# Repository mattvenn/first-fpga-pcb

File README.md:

# Aim

* Make my first PCB with an FPGA
* Keep it super simple and cheap
* Configured by on-board FLASH or direct with a Raspberry Pi
* 6 PMODs, 2 buttons, 2 LEDs, FLASH for configuration bitstreams.

There is also an ECP5 version of this board: https://github.com/mattvenn/basic-ecp5-pcb

# What a Lattice iCE40 FPGA needs

* A clock input. Has to be provided by an oscillator, it doesn't have a crystal driver.
* 1.2v core supply for the internal logic.
* 2.5v non volatile memory supply. Can be provided via a voltage drop over a diode from 3.3v.
* IO supply for the IO pins, different banks of IO can have different supplies. This design uses 3.3v for all banks.
* Get configured over SPI interface. This can be done directly by a microcontroller or a computer, or the bitstream can be programmed into some FLASH, and the FPGA will read it at boot. If FLASH isn't provided then the bitstream needs to be programmed at every power up or configuration reset. 
* Decoupling capacitors for each IO bank.

# PCB

* [Schematic](hardware/schematic.pdf)
* [OHSPark project](https://oshpark.com/shared_projects/wwMxCKlp) or [Gerbers](hardware/first-fpga-pcb-2020-03-09-fab.zip)
* Cheap, 2 layer board. Probably not so good for fast signals.

# BOM

* FPGA iCE40-HX4K-TQ144 (8k accessible with Icestorm tools)
* 3.3v reg TLV73333PDBVT
* 1.2v reg TLV73312PDBVT
* 12MHz oscillator SIT2001BI-S2-33E-12.000000G
* 16MB FLASH IS25LP016D-JBLE (optional).

# Test

See the [test program](test/top.v). This makes a nice pulsing effect on LED2, and LED1 is the slow PWM clock.
The buttons increase or decrease pulsing speed.

    make prog

Yosys and NextPNR are used to create the bitstream and then it's copied to the Raspberry Pi specified
by PI_ADDR in the [Makefile](test/Makefile). 

[Fomu-Flash](https://github.com/im-tomu/fomu-flash) is used to flash the SPI memory, or program the FPGA directly.

# HW V3: bfcbcf7

* fixed mistakenly removed pullups on io2/3 on SPI flash. This made the system vulnerable to noise while FPGA was reading flash.

# HW V2: 444ba78

* removed a few unnecessary pullups on SPI lines - introduced a fault see HW V3.
* connect 4 general purpose pins between Pi & FPGA
* connect additional CS1 pin for SPI comms with Pi
* breakout all Pi pins on separate pins
* shrink board in y axis slightly for even holes and to fit larger Pi boards
* Allow an I2C connection between Pi & FPGA, broken out on pmod p3:
    * Place optional 4k7 pullup resistors R1&R2
    * Setup bitbanged I2C on Raspi on gpios 20 & 21 (pins 38 & 40)
* used FOMU programming pins so default FOMU programming app will work

# HW V1: d9c7cdf

## Errata

* didn't expose a 2nd CS pin so can't communicate with SPI without removing flash 

My fork of [Fomu-Flash](https://github.com/mattvenn/fomu-flash) is used for programming. Fomu-Flash should be able
to reconfigure the pins used with -g, but I couldn't get this to work, so I hard-coded the right pins in this
fork.

# Inspiration

* https://github.com/OLIMEX/iCE40HX1K-EVB/blob/master/iCE40HX1K-EVB_Rev_B.pdf
* https://github.com/icebreaker-fpga/icebreaker/blob/master/hardware/v1.0e/icebreaker-sch.pdf
* icestick

# Reference

* Family datasheet: http://www.latticesemi.com/view_document?document_id=49312
* Programming/FLASH spec: http://www.latticesemi.com/view_document?document_id=46502
* Pinout: http://www.latticesemi.com/view_document?document_id=49383

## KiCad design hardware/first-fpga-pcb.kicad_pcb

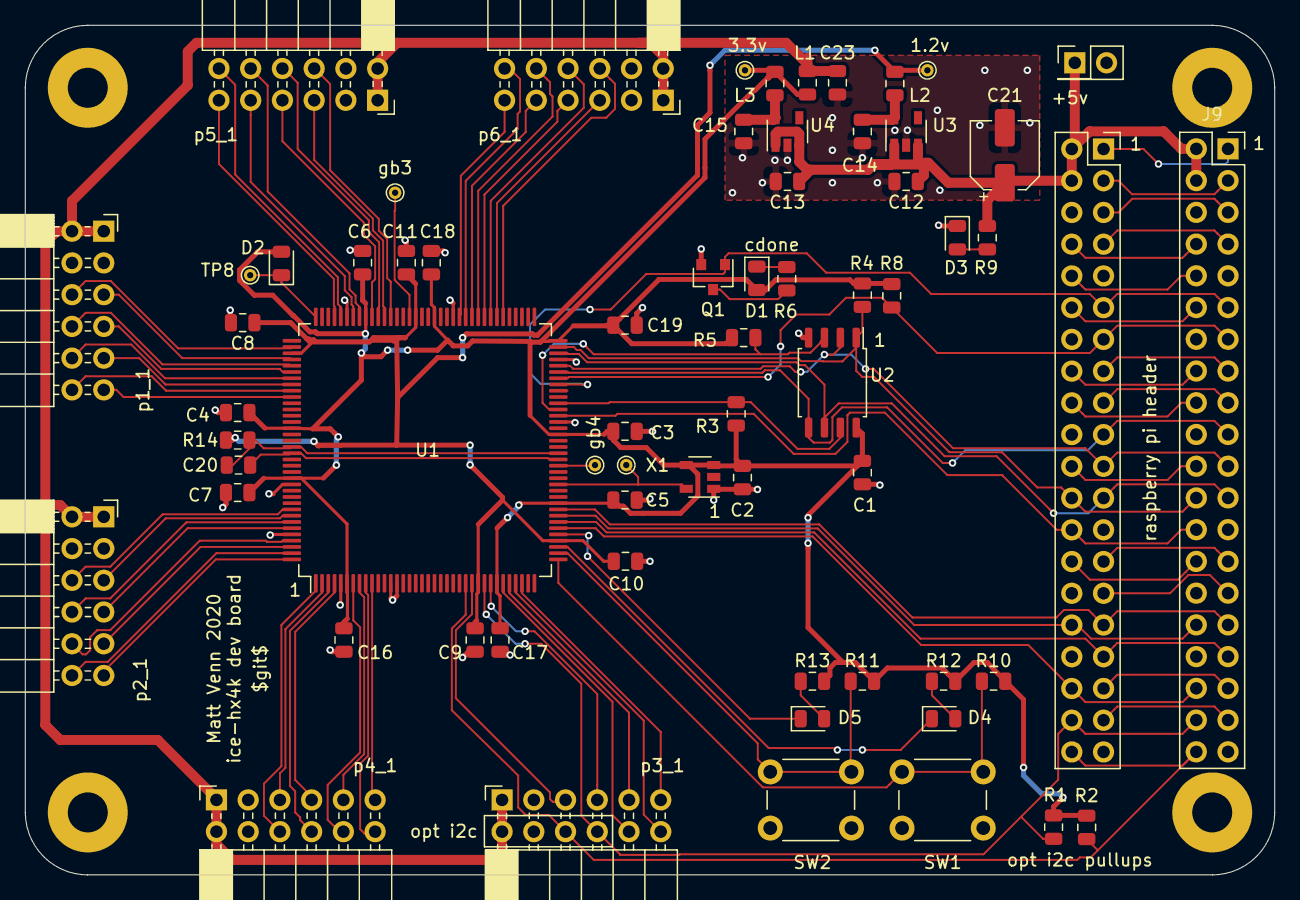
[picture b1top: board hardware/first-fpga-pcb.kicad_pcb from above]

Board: 2 copper layers, 100.0 x 68.0 mm, 70 parts (0 on the bottom side), 100 nets.

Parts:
C1, C2, C3, C4, C5, C6, C7, C8, C9, C10, C11, C16, C17, C18, C19, C20, C23: 100n; C_0805_2012Metric
C12, C13, C14, C15: 1u; C_0805_2012Metric
C21: CP; CP_Elec_5x5.4
D1, D3, D4, D5: LED; LED_0805_2012Metric
D2: D; D_0805_2012Metric
H1, H2, H3, H4: MountingHole_Pad; MountingHole_3.2mm_M3_Pad
J1: Conn_01x02; PinHeader_2x01_P2.54mm_Vertical
J2, J9: Conn_02x20_Odd_Even; PinSocket_2x20_P2.54mm_Vertical
J3, J4, J5, J6, J7, J8: Conn_02x06_Odd_Even; PinSocket_2x06_P2.54mm_Horizontal
L1, L2, L3: L; L_0805_2012Metric
Q1: Q_NMOS_GSD; SOT-23
R1, R2, R3, R4, R5, R8, R10, R11: 10k; R_0805_2012Metric
R6, R9, R12, R13, R14: 200R; R_0805_2012Metric
SW1, SW2: SW_Push; SW_PUSH_6mm
TP1: gbin3; TestPoint_THTPad_D1.0mm_Drill0.5mm
TP2: gbin4; TestPoint_THTPad_D1.0mm_Drill0.5mm
TP5: clock; TestPoint_THTPad_D1.0mm_Drill0.5mm
TP6: 1.2v; TestPoint_THTPad_D1.0mm_Drill0.5mm
TP7: 3.3v; TestPoint_THTPad_D1.0mm_Drill0.5mm
TP8: 2.5v; TestPoint_THTPad_D1.0mm_Drill0.5mm
U1: iCE40-HX4K-TQ144; TQFP-144_20x20mm_P0.5mm
U2: IS25LP016D-JBLE; SOIC-8_5.23x5.23mm_P1.27mm
U3: TLV73312PDBV; SOT-23-5
U4: TLV73333PDBV; SOT-23-5
X1: SiT2001B; SOT-23-5

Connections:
+1V2: C8.1, C9.1, C10.1, C11.1, L2.2, R14.2, TP6.1, U1.27, U1.40, U1.92, U1.111
+3.3VP: C23.1, J3.1, J3.2, J4.1, J4.2, J5.1, J5.2, J6.1, J6.2, J7.1, J7.2, J8.1, J8.2, L1.2
+3V3: C1.1, C2.1, C3.1, C4.1, C5.1, C6.1, C7.1, C16.1, C17.1, C18.1, C19.1, D1.2, D2.2, L1.1, L3.2, R1.1, R2.1, R3.1, R4.1, R5.1, R8.2, R10.2, R11.2, R12.2, R13.2, TP7.1, U1.6, U1.30, U1.46, U1.57, U1.72, U1.89, U1.100, U1.123, U1.131, U2.8, X1.3, X1.4
+5V: C12.1, C13.1, C21.1, J1.1, J2.2, J2.4, J9.2, J9.4, R9.2, U3.1, U3.3, U4.1, U4.3
/1v2: C14.1, L2.1, U3.5
/3v3: C15.1, L3.1, U4.5
/button1: R10.1, SW1.1, U1.37
/button2: R11.1, SW2.1, U1.38
/cdone: J2.11, J9.11, Q1.1, U1.65
/ce1: J2.26, J9.26, U1.60
/clock: TP5.1, U1.49, X1.5
/creset: J2.13, J9.13, R8.1, U1.66
/gp0: J2.27, J9.27
/gp1: J2.28, J9.28
/gp2: J2.3, J9.3
/gp3: J2.5, J9.5
/gp4: J2.7, J9.7
/gp5: J2.29, J9.29
/gp6: J2.31, J9.31, U1.45
/gp8: J2.24, J9.24, R4.2, U1.71, U2.1
/gp9: J2.21, J9.21, U1.68, U2.2
/gp10: J2.19, J9.19, U1.67, U2.5
/gp11: J2.23, J9.23, U1.70, U2.6
/gp12: J2.32, J9.32, U1.44
/gp13: J2.33, J9.33, U1.43
/gp14: J2.8, J9.8
/gp15: J2.10, J9.10
/gp16: J2.36, J9.36, U1.42
/gp18: J2.12, J9.12
/gp19: J2.35, J9.35
/gp20: J2.38, J5.8, J9.38, R1.2, U1.28
/gp21: J2.40, J5.6, J9.40, R2.2, U1.25
/gp22: J2.15, J9.15
/gp23: J2.16, J9.16
/gp24: J2.18, J9.18
/gp25: J2.22, J9.22
/gp26: J2.37, J9.37
/led1: D4.1, U1.39
/led2: D5.1, U1.41
/p1_1: J3.11, U1.118
/p1_2: J3.9, U1.116
/p1_3: J3.7, U1.114
/p1_4: J3.5, U1.112
/p1_7: J3.12, U1.117
/p1_8: J3.10, U1.115
/p1_9: J3.8, U1.113
/p1_10: J3.6, U1.110
/p2_1: J4.11, U1.144
/p2_2: J4.9, U1.142
/p2_3: J4.7, U1.139
/p2_4: J4.5, U1.137
/p2_7: J4.12, U1.143
/p2_8: J4.10, U1.141
/p2_9: J4.8, U1.138
/p2_10: J4.6, U1.136
/p3_1: J5.11, U1.34
/p3_2: J5.9, U1.32
/p3_3: J5.7, U1.29
/p3_4: J5.5, U1.26
/p3_7: J5.12, U1.33
/p3_8: J5.10, U1.31
/p4_1: J6.11, U1.10
/p4_2: J6.9, U1.8
/p4_3: J6.7, U1.4
/p4_4: J6.5, U1.2
/p4_7: J6.12, U1.9
/p4_8: J6.10, U1.7
/p4_9: J6.8, U1.3
/p4_10: J6.6, U1.1
/p5_1: J7.11, U1.105
/p5_2: J7.9, U1.102
/p5_3: J7.7, U1.99
/p5_4: J7.5, U1.97
/p5_7: J7.12, U1.104
/p5_8: J7.10, U1.101
/p5_9: J7.8, U1.98
/p5_10: J7.6, U1.96
/p6_1: J8.11, U1.85
/p6_2: J8.9, U1.83
/p6_3: J8.7, U1.81
/p6_4: J8.5, U1.79
/p6_7: J8.12, U1.84
/p6_8: J8.10, U1.82
/p6_9: J8.8, U1.80
/p6_10: J8.6, U1.78
/pi_3v3: J2.1, J9.1
/pi_3v3_2: J2.17, J9.17
/sd_io2: R5.2, U1.61, U2.3
/sd_io3: R3.2, U1.62, U2.7
/vcc_pll: C20.1, R14.1, U1.54, U1.126
GND: C1.2, C2.2, C3.2, C4.2, C5.2, C6.2, C7.2, C8.2, C9.2, C10.2, C11.2, C12.2, C13.2, C14.2, C15.2, C16.2, C17.2, C18.2, C19.2, C21.2, C23.2, D3.1, H1.1, H2.1, H3.1, H4.1, J1.2, J2.6, J2.9, J2.14, J2.20, J2.25, J2.30, J2.34, J2.39, J3.3, J3.4, J4.3, J4.4, J5.3, J5.4, J6.3, J6.4, J7.3, J7.4, J8.3, J8.4, J9.6, J9.9, J9.14, J9.20, J9.25, J9.30, J9.34, J9.39, Q1.2, SW1.2, SW2.2, U1.5, U1.13, U1.14, U1.59, U1.69, U1.86, U1.103, U1.132, U1.140, U2.4, U3.2, U4.2, X1.1
unnamed: C20.2, U1.53, U1.127
unnamed: D1.1, R6.1
unnamed: D2.1, TP8.1, U1.108
unnamed: D3.2, R9.1
unnamed: D4.2, R12.1
unnamed: D5.2, R13.1
unnamed: Q1.3, R6.2
unnamed: TP1.1, U1.93
unnamed: TP2.1, U1.52

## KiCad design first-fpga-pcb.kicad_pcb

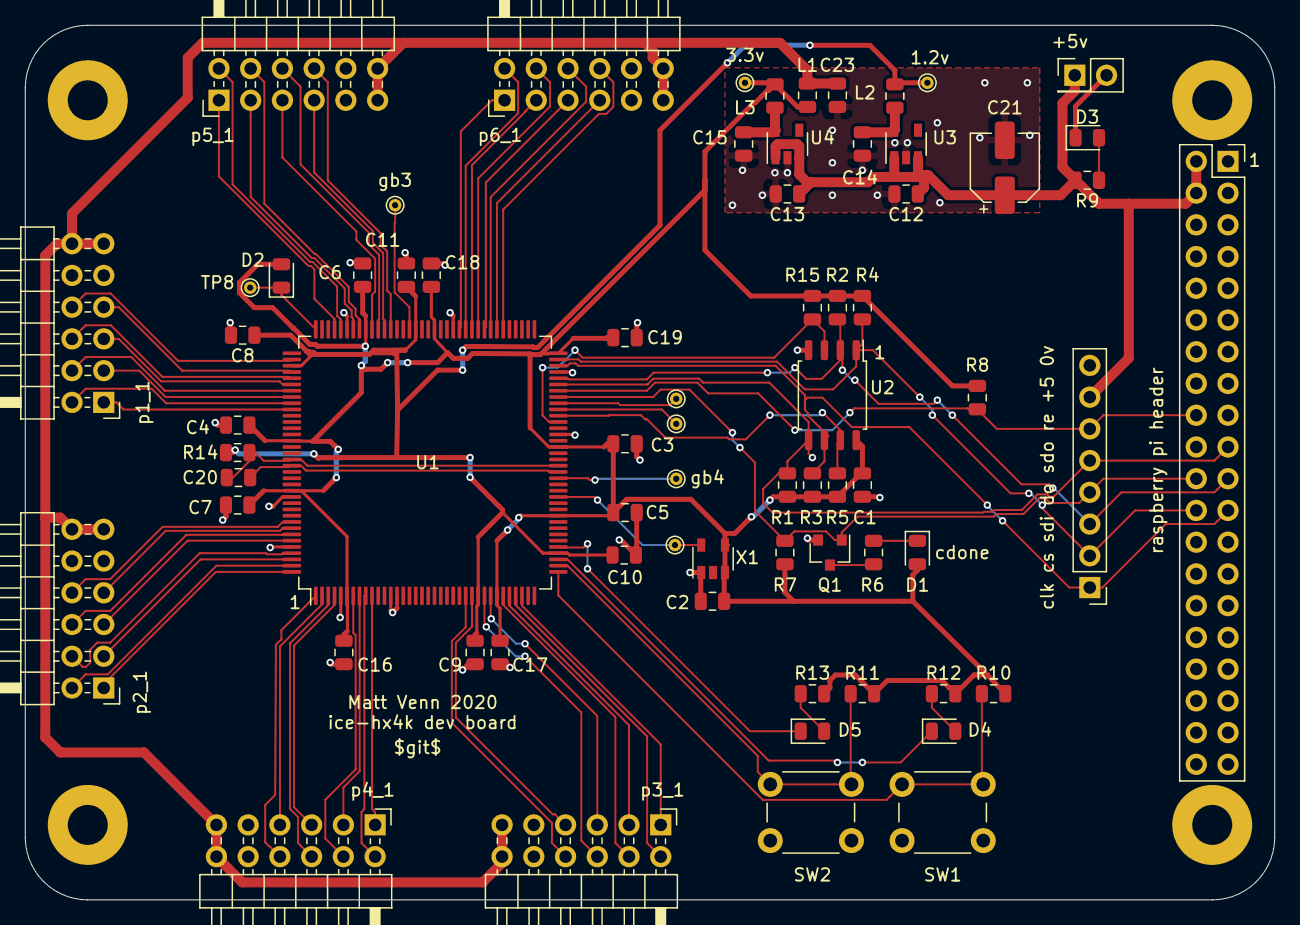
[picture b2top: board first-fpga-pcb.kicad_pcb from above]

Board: 2 copper layers, 100.0 x 70.0 mm, 74 parts (0 on the bottom side), 80 nets.

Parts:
C1, C2, C3, C4, C5, C6, C7, C8, C9, C10, C11, C16, C17, C18, C19, C20, C23: 100n; C_0805_2012Metric
C12, C13, C14, C15: 1u; C_0805_2012Metric
C21: CP; CP_Elec_5x5.4
D1, D3, D4, D5: LED; LED_0805_2012Metric
D2: D; D_0805_2012Metric
H1, H2, H3, H4: MountingHole_Pad; MountingHole_3.2mm_M3_Pad
J1: Conn_01x02; PinHeader_2x01_P2.54mm_Vertical
J2: Conn_01x08; PinHeader_1x08_P2.54mm_Vertical
J3, J4, J5, J6, J7, J8: Conn_02x06_Odd_Even; PinHeader_2x06_P2.54mm_Horizontal
J9: Conn_02x20_Odd_Even; PinSocket_2x20_P2.54mm_Vertical
L1, L2, L3: L; L_0805_2012Metric
Q1: Q_NMOS_GSD; SOT-23
R1, R2, R3, R5, R7, R15: dnp; R_0805_2012Metric
R4, R8, R10, R11: 10k; R_0805_2012Metric
R6, R9, R12, R13, R14: 200R; R_0805_2012Metric
SW1, SW2: SW_Push; SW_PUSH_6mm
TP1: gbin3; TestPoint_THTPad_D1.0mm_Drill0.5mm
TP2: gbin4; TestPoint_THTPad_D1.0mm_Drill0.5mm
TP3: cbsel0; TestPoint_THTPad_D1.0mm_Drill0.5mm
TP4: cbsel1; TestPoint_THTPad_D1.0mm_Drill0.5mm
TP5: clock; TestPoint_THTPad_D1.0mm_Drill0.5mm
TP6: 1.2v; TestPoint_THTPad_D1.0mm_Drill0.5mm
TP7: 3.3v; TestPoint_THTPad_D1.0mm_Drill0.5mm
TP8: 2.5v; TestPoint_THTPad_D1.0mm_Drill0.5mm
U1: iCE40-HX4K-TQ144; TQFP-144_20x20mm_P0.5mm
U2: IS25LP016D-JBLE; SOIC-8_5.23x5.23mm_P1.27mm
U3: TLV73312PDBV; SOT-23-5
U4: TLV73333PDBV; SOT-23-5
X1: SiT2001B; SOT-23-5

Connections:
+1V2: C8.1, C9.1, C10.1, C11.1, L2.2, R14.2, TP6.1, U1.27, U1.40, U1.92, U1.111
+3.3VP: C23.1, J3.11, J3.12, J4.11, J4.12, J5.11, J5.12, J6.11, J6.12, J7.11, J7.12, J8.11, J8.12, L1.2
+3V3: C1.1, C2.1, C3.1, C4.1, C5.1, C6.1, C7.1, C16.1, C17.1, C18.1, C19.1, D1.2, D2.2, L1.1, L3.2, R1.2, R2.2, R3.2, R4.2, R5.2, R7.2, R8.2, R10.2, R11.2, R12.2, R13.2, R15.2, TP7.1, U1.6, U1.30, U1.46, U1.57, U1.72, U1.89, U1.100, U1.123, U1.131, U2.8, X1.3, X1.4
+5V: C12.1, C13.1, C21.1, J1.1, J2.7, J9.2, J9.4, R9.2, U3.1, U3.3, U4.1, U4.3
/1v2: C14.1, L2.1, U3.5
/3v3: C15.1, L3.1, U4.5
/button1: R10.1, SW1.1, U1.37
/button2: R11.1, SW2.1, U1.38
/cdone: J2.4, J9.22, Q1.1, R7.1, U1.65
/clock: TP5.1, U1.49, X1.5
/creset: J2.6, J9.18, R8.1, U1.66
/led1: D4.1, U1.39
/led2: D5.1, U1.41
/p1_1: J3.1, U1.118
/p1_2: J3.3, U1.116
/p1_3: J3.5, U1.114
/p1_4: J3.7, U1.112
/p1_7: J3.2, U1.117
/p1_8: J3.4, U1.115
/p1_9: J3.6, U1.113
/p1_10: J3.8, U1.110
/p2_1: J4.1, U1.144
/p2_2: J4.3, U1.142
/p2_3: J4.5, U1.139
/p2_4: J4.7, U1.137
/p2_7: J4.2, U1.143
/p2_8: J4.4, U1.141
/p2_9: J4.6, U1.138
/p2_10: J4.8, U1.136
/p3_1: J5.1, U1.34
/p3_2: J5.3, U1.32
/p3_3: J5.5, U1.29
/p3_4: J5.7, U1.26
/p3_7: J5.2, U1.33
/p3_8: J5.4, U1.31
/p3_9: J5.6, U1.28
/p3_10: J5.8, U1.25
/p4_1: J6.1, U1.10
/p4_2: J6.3, U1.8
/p4_3: J6.5, U1.4
/p4_4: J6.7, U1.2
/p4_7: J6.2, U1.9
/p4_8: J6.4, U1.7
/p4_9: J6.6, U1.3
/p4_10: J6.8, U1.1
/p5_1: J7.1, U1.105
/p5_2: J7.3, U1.102
/p5_3: J7.5, U1.99
/p5_4: J7.7, U1.97
/p5_7: J7.2, U1.104
/p5_8: J7.4, U1.101
/p5_9: J7.6, U1.98
/p5_10: J7.8, U1.96
/p6_1: J8.1, U1.85
/p6_2: J8.3, U1.83
/p6_3: J8.5, U1.81
/p6_4: J8.7, U1.79
/p6_7: J8.2, U1.84
/p6_8: J8.4, U1.82
/p6_9: J8.6, U1.80
/p6_10: J8.8, U1.78
/sd_clk: J2.1, J9.23, R3.1, U1.70, U2.6
/sd_cs: J2.2, J9.24, R4.1, U1.71, U2.1
/sd_io2: R15.1, U1.61, U2.3
/sd_io3: R5.1, U1.62, U2.7
/sdi: J2.3, J9.21, R2.1, U1.68, U2.2
/sdo: J2.5, J9.19, R1.1, U1.67, U2.5
/vcc_pll: C20.1, R14.1, U1.54, U1.126
GND: C1.2, C2.2, C3.2, C4.2, C5.2, C6.2, C7.2, C8.2, C9.2, C10.2, C11.2, C12.2, C13.2, C14.2, C15.2, C16.2, C17.2, C18.2, C19.2, C21.2, C23.2, D3.1, H1.1, H2.1, H3.1, H4.1, J1.2, J2.8, J3.9, J3.10, J4.9, J4.10, J5.9, J5.10, J6.9, J6.10, J7.9, J7.10, J8.9, J8.10, J9.6, J9.20, J9.25, Q1.2, SW1.2, SW2.2, U1.5, U1.13, U1.14, U1.59, U1.69, U1.86, U1.103, U1.132, U1.140, U2.4, U3.2, U4.2, X1.1
unnamed: C20.2, U1.53, U1.127
unnamed: D1.1, R6.1
unnamed: D2.1, TP8.1, U1.108
unnamed: D3.2, R9.1
unnamed: D4.2, R12.1
unnamed: D5.2, R13.1
unnamed: Q1.3, R6.2
unnamed: TP1.1, U1.93
unnamed: TP2.1, U1.52
unnamed: TP3.1, U1.63
unnamed: TP4.1, U1.64

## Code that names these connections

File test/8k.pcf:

set_io -nowarn sw1      37
set_io -nowarn sw2      38
set_io -nowarn led1     39
set_io -nowarn led2     41
set_io -nowarn clk      49

set_io -nowarn pmod6_10 78
set_io -nowarn pmod6_4  79
set_io -nowarn pmod6_9  80
set_io -nowarn pmod6_3  81
set_io -nowarn pmod6_8  82
set_io -nowarn pmod6_2  83
set_io -nowarn pmod6_7  84
set_io -nowarn pmod6_1  85

set_io -nowarn gbin3    93

set_io -nowarn pmod5_10 96
set_io -nowarn pmod5_4  97
set_io -nowarn pmod5_9  98
set_io -nowarn pmod5_3  99
set_io -nowarn pmod5_8  101
set_io -nowarn pmod5_2  102
set_io -nowarn pmod5_7  104
set_io -nowarn pmod5_1  105

# extra pins for qspi
set_io -nowarn sd_io2   61
set_io -nowarn sd_io3   62
set_io -nowarn sd_cs    71  # connected to Raspi gpio8  (ce0)
set_io -nowarn sd_sck   70  # connected to Raspi gp11   (clk)
set_io -nowarn sd_sdi   68  # connected to Raspi gpio9  (miso)
set_io -nowarn sd_sdo   67  # connected to Raspi gpio10 (mosi)

# extra GPIO pins for Raspi comms
set_io -nowarn gpio16   42  # connected to Raspi gpio16
set_io -nowarn gpio13   43  # connected to Raspi gpio13
set_io -nowarn gpio12   44  # connected to Raspi gpio12
set_io -nowarn gpio6    45  # connected to Raspi gpio6
set_io -nowarn gpio7    60  # connected to Raspi gpio7  (ce1)

set_io -nowarn pmod1_10 110
set_io -nowarn pmod1_4  112
set_io -nowarn pmod1_9  113
set_io -nowarn pmod1_3  114
set_io -nowarn pmod1_8  115
set_io -nowarn pmod1_2  116
set_io -nowarn pmod1_7  117
set_io -nowarn pmod1_1  118

set_io -nowarn pmod2_10 136
set_io -nowarn pmod2_4  137
set_io -nowarn pmod2_9  138
set_io -nowarn pmod2_3  139
set_io -nowarn pmod2_8  141
set_io -nowarn pmod2_2  142
set_io -nowarn pmod2_7  143
set_io -nowarn pmod2_1  144

set_io -nowarn pmod4_10 1
set_io -nowarn pmod4_4  2
set_io -nowarn pmod4_9  3
set_io -nowarn pmod4_3  4
set_io -nowarn pmod4_8  7
set_io -nowarn pmod4_2  8
set_io -nowarn pmod4_7  9
set_io -nowarn pmod4_1  10

set_io -nowarn pmod3_10 25 # can put a pull up on R2 for I2C. Connected to Raspi gpio21. Need to setup bitbanged I2C on Raspi on this pin.
set_io -nowarn pmod3_4  26
set_io -nowarn pmod3_9  28 # can put a pull up on R1 for I2C. Connected to Raspi gpio20. Need to setup bitbanged I2C on Raspi on this pin.
set_io -nowarn pmod3_3  29
set_io -nowarn pmod3_8  31
set_io -nowarn pmod3_2  32
set_io -nowarn pmod3_7  33
set_io -nowarn pmod3_1  34

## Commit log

2019-12-30 neaten schematic
2019-12-30 schematic pdf
2019-12-30 readme
2019-12-30 add lattice lib as submodule
2019-12-30 changed to 144 pin package for PLL, added more PMODs, chose FLASH part, updated README
2019-12-30 use submodule
2019-12-30 updated schematic
2019-12-30 fixed PLL gnd connected to board gnd
2019-12-30 starting layout
2019-12-31 change to 4k and finish routing
2019-12-31 update schematic and readme
2019-12-31 added raspi header, fattened psu traces, moved psu to top
2020-01-01 changed flash orientation for better routing, fixed upside down header
2020-01-01 config for autofab
2020-01-10 hard coded reset pin
2020-01-10 test program
2020-01-10 gpio numbering notes on Raspi Header
2020-01-10 add notes to readme and fix top
2020-01-10 add pin numbers for all pmods
2020-01-10 spi pins
2020-01-10 update schematic with raspi gpio pin notes
2020-01-10 note on 8k and Makefile
2020-01-10 added gerbers
2020-01-10 move board png
2020-01-10 add schematic to readme
2020-01-10 add link to gerbers and ohspark
2020-01-10 minor edits
2020-01-10 what an fpga needs section
2020-01-13 PLL test
2020-01-13 split rule for prog fpga and prog flash
2020-01-17 pwm led
2020-01-17 add gamma correction
2020-01-17 gamma
2020-01-17 create gamma.hex with Makefile
2020-01-21 notes on todos
2020-01-21 make gui
2020-03-09 fixed a few things and added features as detailed in README.md
2020-03-09 added new gerbers
2020-03-09 added new hw git
2020-03-09 fomu notes
2020-03-24 change pmod to female
2020-03-24 pwm_width as a -D variable
2020-03-25 updated docs and pcf
2020-03-25 make gamma configurable in Makefile, show PWM slow clock on LED1
2020-03-25 image link
2020-03-25 remove submodule for fomuflash
2020-03-25 updated schematic, linked new gerbers and oshpark project in README
2020-07-17 fixed missing hold resistor
2020-07-17 updated schematic and added git ref to readme of v3 hw
2020-08-03 add link to ecp5 version
2020-08-03 fix link
